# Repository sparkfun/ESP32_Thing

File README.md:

SparkFun ESP32 Thing
========================================

[*SparkFun ESP32 Thing (DEV-13907)*](https://www.sparkfun.com/products/13907)

The [SparkFun ESP32 Thing](https://www.sparkfun.com/products/13907) is a comprehensive development platform for Espressif’s ESP32, their super-charged version of the popular ESP8266. Like the 8266, the ESP32 is a WiFi-compatible microcontroller but adds nearly 30 I/O pins. The ESP32’s power and versatility will make it the foundation of IoT and connected projects for many years to come.

Why the name? We lovingly call it the “Thing” because it's the perfect foundation for your Internet of Things project. The Thing does everything from turning on an LED to posting data with your chosen platform, and can be programmed just like any microcontroller. You can even program the Thing through the Arduino IDE by installing the [ESP32 Arduino Core](https://learn.sparkfun.com/tutorials/esp32-thing-hookup-guide#installing-the-esp32-arduino-core).

The SparkFun ESP32 Thing equips the ESP32 with everything necessary to program, run and develop on the wonderchip. In addition to the WiFi SoC, the Thing includes an FTDI FT231x, which converts USB to serial, and allows your computer to program and communicate with the microcontroller. It also features a LiPo charger, so your ESP32 project can be battery-powered and truly wireless. Additionally, the board includes a handful of LEDs and buttons to aid in your development.

Repository Contents
-------------------

* **/Hardware** - Eagle design files (.brd, .sch)
* **/Production** - Production panel files (.brd)

Documentation
--------------
* **[Hookup Guide](https://learn.sparkfun.com/tutorials/esp32-thing-hookup-guide)** - Basic hookup guide for the ESP32 Thing.
* **[SparkFun Fritzing repo](https://github.com/sparkfun/Fritzing_Parts)** - Fritzing diagrams for SparkFun products.
* **[SparkFun 3D Model repo](https://github.com/sparkfun/3D_Models)** - 3D models of SparkFun products. 
* **[SparkFun Graphical Datasheets](https://github.com/sparkfun/Graphical_Datasheets)** -Graphical Datasheets for various SparkFun products.

Product Versions
----------------
* [DEV-13907](https://www.sparkfun.com/products/13907) - Initial release of the ESP32 Thing.

Version History
---------------
* [V_1.0](https://github.com/sparkfun/ESP32_Thing/releases/tag/V_1.0) - Initial release of the ESP32 Thing

License Information
-------------------

This product is _**open source**_! 

Please review the LICENSE.md file for license information. 

If you have any questions or concerns on licensing, please contact technical support on our [SparkFun forums](https://forum.sparkfun.com/viewforum.php?f=152).

Distributed as-is; no warranty is given.

- Your friends at SparkFun.

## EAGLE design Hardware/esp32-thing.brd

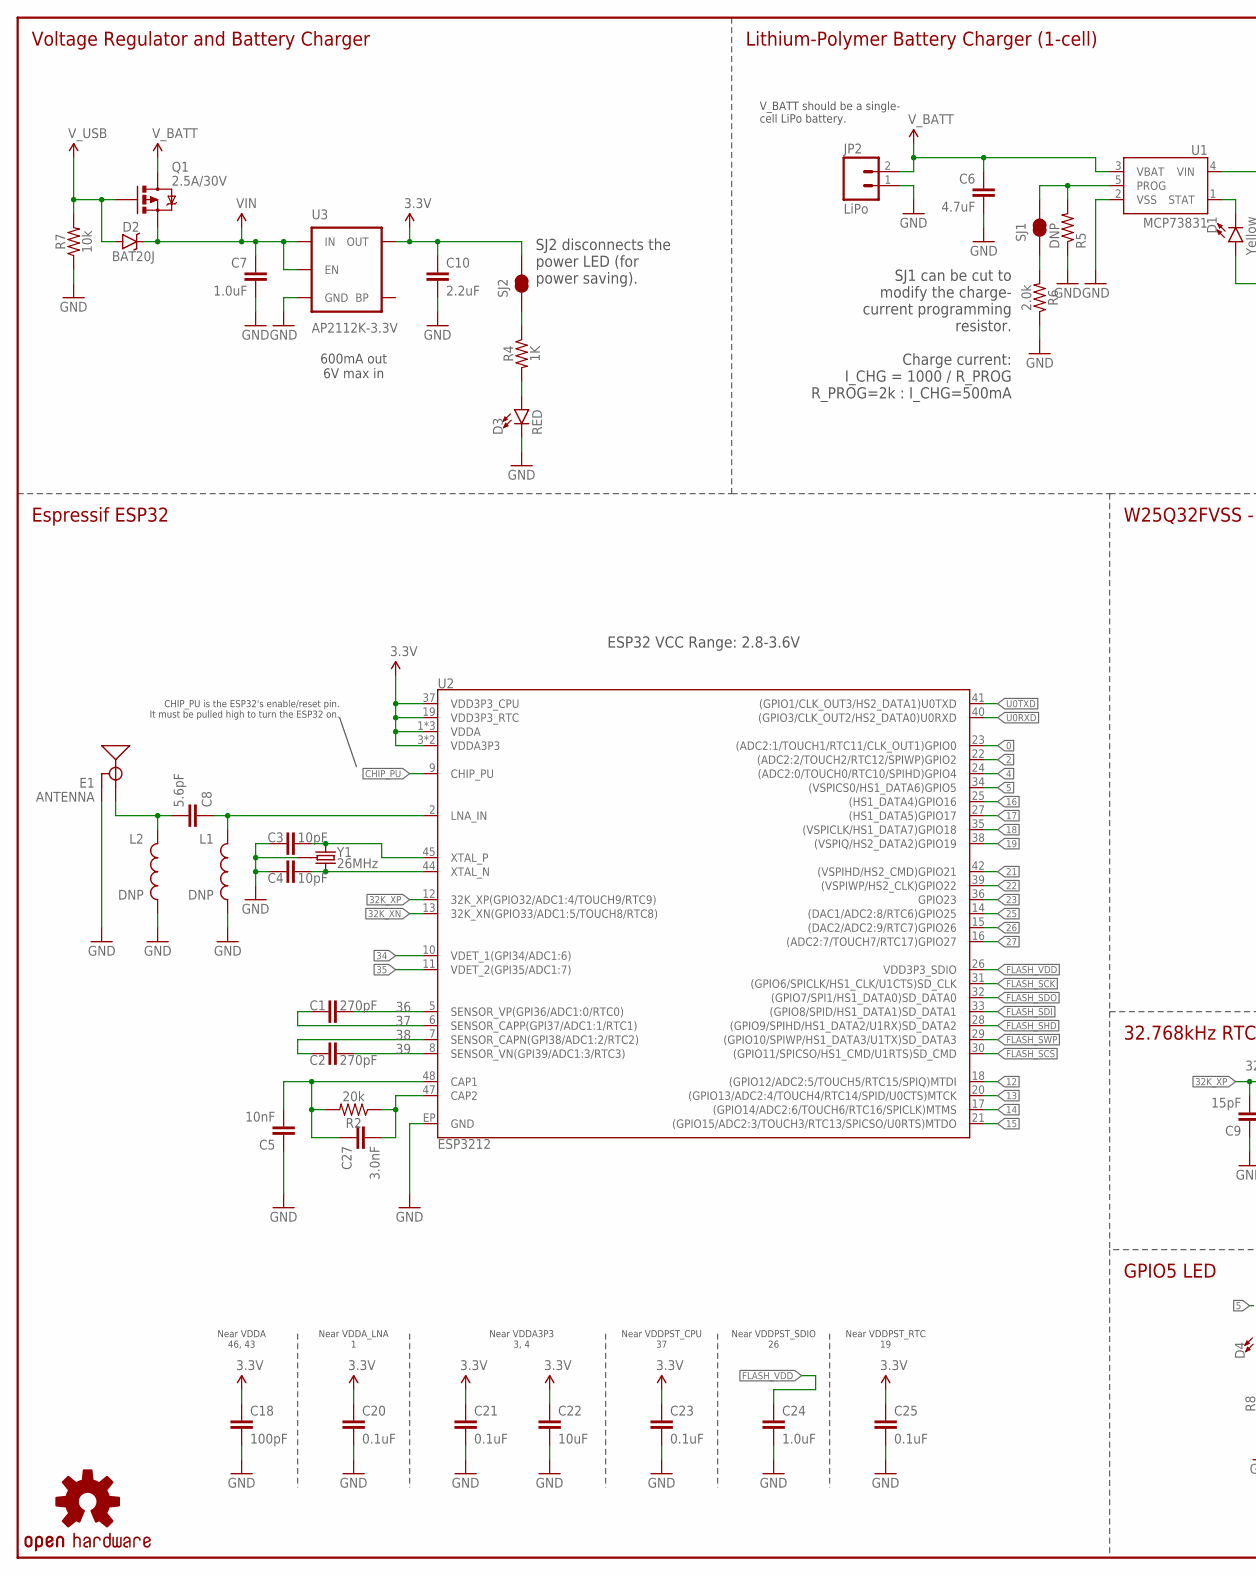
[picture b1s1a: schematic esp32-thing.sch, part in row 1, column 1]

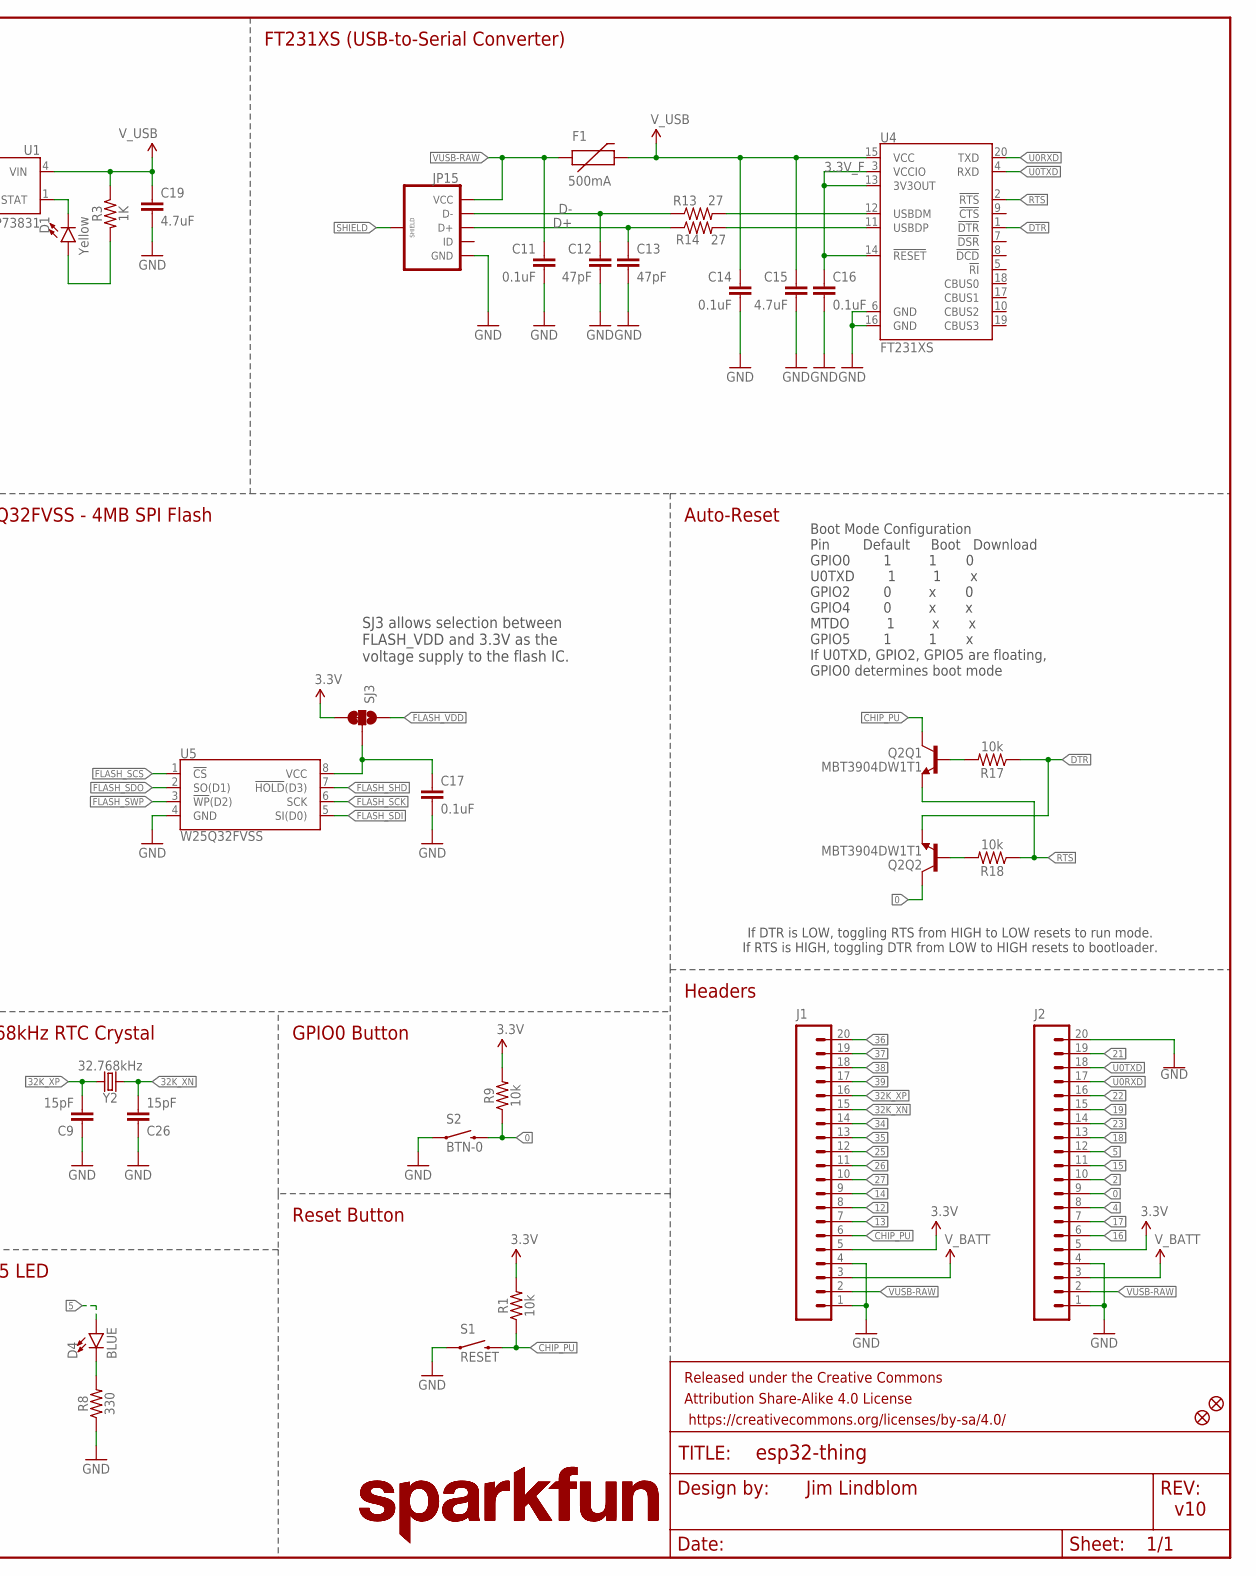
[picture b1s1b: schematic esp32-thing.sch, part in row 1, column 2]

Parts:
C1, C2: 270pF; 0603
C3, C4: 10pF; 0603
C5: 10nF; 0603
C6, C19: 4.7uF; 0603
C7: 1.0uF; 0805
C8: 5.6pF; 0603
C9, C26: 15pF; 0603
C10: 2.2uF; 0603
C11, C14, C16, C17, C20, C21, C23, C25: 0.1uF; 0603
C12, C13: 47pF; 0603
C15: 4.7uF; 0603-CAP
C18: 100pF; 0603
C22: 10uF; 0603
C24: 1.0uF; 0603
C27: 3.0nF; 0603
D1: Yellow; LED-0603
D2: BAT20J; SOD-323
D3: RED; LED-0603
D4: BLUE; LED-0603
E1: ANTENNA; TRACE_ANTENNA_2.4GHZ_25.7MM_TUNED
F1: 500mA; PTC-1206
FD1, FD2: FIDUCIALUFIDUCIAL; MICRO-FIDUCIAL
FRAME1: FRAME-LEDGER; CREATIVE_COMMONS
J1, J2: M20NOSILK; 1X20_NOSILK
JP2: LiPo; JST-2-PTH
JP15: USB_MICROB_PLUGCONN-11752; USB-B-MICRO-SMD_V03
L1, L2: DNP; 0603
LOGO1, LOGO3: SFE_LOGO_NAME.2_INCH; SFE_LOGO_NAME_.2
LOGO2: OSHW-LOGOMINI; OSHW-LOGO-MINI
Q1: 2.5A/30V; SOT23-3
Q2: MBT3904DW1T1; SC70-6
R1, R7, R9, R17, R18: 10k; 0603
R2: 20k; 0603
R3, R4: 1K; 0603
R5: DNP; 1/6W-RES
R6: 2.0k; 0603
R8: 330; 0603
R13, R14: 27; 0603
S1: RESET; TACTILE_SWITCH_SMD_4.6X2.8MM
S2: BTN-0; TACTILE_SWITCH_SMD_4.6X2.8MM
SJ1, SJ2: JUMPER-PAD-2-NC_BY_TRACE; PAD-JUMPER-2-NC_BY_TRACE_YES_SILK
SJ3: JUMPER-PAD-3-2OF3_NC_BY_TRACE_SMALL; PAD-JUMPER-3-2OF3_NC_BY_TRACE_YES_SILK_FULL_BOX
U1: MCP73831; SOT23-5
U2: ESP3212; QFN48-0.4MM
U3: AP2112K-3.3V; SOT23-5
U4: FT231XS; SSOP20_L
U5: W25Q32FVSS; SOIC-8
Y1: 26MHz; CRYSTAL-SMD-3.2X2.5
Y2: 32.768kHz; CRYSTAL-SMD-3.2X1.5MM

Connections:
0: J2.9, Q2.6 (C), R9.1, S2.3 (2), S2.4 (2), U2.23 ((ADC2:1/TOUCH1/RTC11/CLK_OUT1)GPIO0)
2: J2.10, U2.22 ((ADC2:2/TOUCH2/RTC12/SPIWP)GPIO2)
3.3V: C10.1, C18.1, C20.1, C21.1, C22.1, C23.1, C25.1, J1.5, J2.5, R1.2, R9.2, SJ2.2, SJ3.3, U2.1 (VDDA), U2.3 (VDDA3P3), U2.4 (VDDA3P3), U2.19 (VDD3P3_RTC), U2.37 (VDD3P3_CPU), U2.43 (VDDA), U2.46 (VDDA), U3.5 (OUT)
3.3V_F: C16.1, U4.3 (VCCIO), U4.13 (3V3OUT), U4.14 (!RESET)
4: J2.8, U2.24 ((ADC2:0/TOUCH0/RTC10/SPIHD)GPIO4)
5: D4.A, J2.12, U2.34 ((VSPICS0/HS1_DATA6)GPIO5)
12: J1.8, U2.18 ((GPIO12/ADC2:5/TOUCH5/RTC15/SPIQ)MTDI)
13: J1.7, U2.20 ((GPIO13/ADC2:4/TOUCH4/RTC14/SPID/U0CTS)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)
14: J1.9, U2.17 ((GPIO14/ADC2:6/TOUCH6/RTC16/SPICLK)MTMS)
15: J2.11, U2.21 ((GPIO15/ADC2:3/TOUCH3/RTC13/SPICSO/U0RT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)
16: J2.6, U2.25 ((HS1_DATA4)GPIO16)
17: J2.7, U2.27 ((HS1_DATA5)GPIO17)
18: J2.13, U2.35 ((VSPICLK/HS1_DATA7)GPIO18)
19: J2.15, U2.38 ((VSPIQ/HS2_DATA2)GPIO19)
21: J2.19, U2.42 ((VSPIHD/HS2_CMD)GPIO21)
22: J2.16, U2.39 ((VSPIWP/HS2_CLK)GPIO22)
23: J2.14, U2.36 (GPIO23)
25: J1.12, U2.14 ((DAC1/ADC2:8/RTC6)GPIO25)
26: J1.11, U2.15 ((DAC2/ADC2:9/RTC7)GPIO26)
27: J1.10, U2.16 ((ADC2:7/TOUCH7/RTC17)GPIO27)
32K_XN: C26.2, J1.15, U2.13 (32K_XN(GPIO33/ADC1:5/TOUCH8/RTC8)), Y2.P$2 (2)
32K_XP: C9.2, J1.16, U2.12 (32K_XP(GPIO32/ADC1:4/TOUCH9/RTC9)), Y2.P$1 (1)
34: J1.14, U2.10 (VDET_1(GPI34/ADC1:6))
35: J1.13, U2.11 (VDET_2(GPI35/ADC1:7))
36: C1.2, J1.20, U2.5 (SENSOR_VP(GPI36/ADC1:0/RTC0))
37: C1.1, J1.19, U2.6 (SENSOR_CAPP(GPI37/ADC1:1/RTC1))
38: C2.1, J1.18, U2.7 (SENSOR_CAPN(GPI38/ADC1:2/RTC2))
39: C2.2, J1.17, U2.8 (SENSOR_VN(GPI39/ADC1:3/RTC3))
CAP_10N: C5.2, C27.1, R2.2, U2.48 (CAP1)
CHIP_PU: J1.6, Q2.3 (C), R1.1, S1.3 (2), S1.4 (2), U2.9 (CHIP_PU)
D+: C13.1, JP15.D+, R14.1
D-: C12.1, JP15.D-, R13.1
DTR: Q2.1 (E), R17.1, U4.1 (!DTR)
FLASH_SCK: U2.31 ((GPIO6/SPICLK/HS1_CLK/U1CTS)SD_CLK), U5.6 (SCK)
FLASH_SCS: U2.30 ((GPIO11/SPICSO/HS1_CMD/U1RTS)SD_CMD), U5.1 (!CS!)
FLASH_SDI: U2.33 ((GPIO8/SPID/HS1_DATA1)SD_DATA1), U5.5 (SI(D0))
FLASH_SDO: U2.32 ((GPIO7/SPI1/HS1_DATA0)SD_DATA0), U5.2 (SO(D1))
FLASH_SHD: U2.28 ((GPIO9/SPIHD/HS1_DATA2/U1RX)SD_DATA2), U5.7 (!HOLD!(D3))
FLASH_SWP: U2.29 ((GPIO10/SPIWP/HS1_DATA3/U1TX)SD_DATA3), U5.3 (!WP!(D2))
FLASH_VDD: C24.1, SJ3.1, U2.26 (VDD3P3_SDIO)
GND: C3.1, C4.1, C5.1, C6.2, C7.2, C9.1, C10.2, C11.2, C12.2, C13.2, C14.2, C15.2, C16.2, C17.2, C18.2, C19.2, C20.2, C21.2, C22.2, C23.2, C24.2, C25.2, C26.1, D3.C, E1.GND, E1.GND2 (GND), J1.1, J1.4, J2.1, J2.4, J2.20, JP2.1, JP15.GND, L1.2, L2.2, R5.1, R6.1, R7.1, R8.1, S1.1, S1.2 (1), S2.1, S2.2 (1), U1.2 (VSS), U2.EP (GND), U3.2 (GND), U4.6 (GND), U4.16 (GND), U5.4 (GND), Y1.2 (GND), Y1.4 (GND)
LNA_IN: C8.1, L1.1, U2.2 (LNA_IN)
unnamed: D4.C, R8.2
unnamed: D3.A, R4.2
unnamed: R4.1, SJ2.1
unnamed: C27.2, R2.1, U2.47 (CAP2)
unnamed: R13.2, U4.12 (USBDM)
unnamed: R14.2, U4.11 (USBDP)
unnamed: D1.C, U1.1 (STAT)
unnamed: Q2.5 (B), R17.2
unnamed: C17.1, SJ3.2, U5.8 (VCC)
unnamed: Q2.2 (B), R18.2
unnamed: C3.2, U2.45 (XTAL_P), Y1.1
unnamed: R5.2, SJ1.2, U1.5 (PROG)
unnamed: C4.2, U2.44 (XTAL_N), Y1.3 (2)
unnamed: R6.2, SJ1.1
unnamed: D1.A, R3.2
RTS: Q2.4 (E), R18.1, U4.2 (!RTS)
SHIELD: JP15.SHIELD1 (SHIELD), JP15.SHIELD2 (SHIELD), JP15.SHIELD3 (SHIELD)
TRACE_ANT: C8.2, E1.ANT (SIGNAL), L2.1
U0RXD: J2.17, U2.40 ((GPIO3/CLK_OUT2/HS2_DATA0)U0RXD), U4.20 (TXD)
U0TXD: J2.18, U2.41 ((GPIO1/CLK_OUT3/HS2_DATA1)U0TXD), U4.4 (RXD)
VIN: C7.1, D2.C, Q1.2 (S), U3.1 (IN), U3.3 (EN)
VUSB-RAW: C11.1, F1.1, J1.2, J2.2, JP15.VBUS (VCC)
V_BATT: C6.1, J1.3, J2.3, JP2.2, Q1.3 (D), U1.3 (VBAT)
V_USB: C14.1, C15.1, C19.1, D2.A, F1.2, Q1.1 (G), R3.1, R7.2, U1.4 (VIN), U4.15 (VCC)

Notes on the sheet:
Boot Mode Configuration Pin Default Boot Download GPIO0 1 1 0 U0TXD 1 1 x GPIO2 0 x 0 GPIO4 0 x x MTDO 1 x x GPIO5 1 1 x If U0TXD, GPIO2, GPIO5 are floating, GPIO0 determines boot mode
FT231XS (USB-to-Serial Converter)
V_BATT should be a single- cell LiPo battery.
Charge current: I_CHG = 1000 / R_PROG R_PROG=2k : I_CHG=500mA
Voltage Regulator and Battery Charger
SJ1 can be cut to modify the charge- current programming resistor.
Lithium-Polymer Battery Charger (1-cell)
600mA out 6V max in
Auto-Reset
Near VDDA 46, 43
Near VDDA_LNA 1
Near VDDA3P3 3, 4
Near VDDPST_CPU 37
Near VDDPST_SDIO 26
Near VDDPST_RTC 19
Espressif ESP32
W25Q32FVSS - 4MB SPI Flash
32.768kHz RTC Crystal
GPIO0 Button
Reset Button
GPIO5 LED
Headers
v10
Jim Lindblom
ESP32 VCC Range: 2.8-3.6V
SJ3 allows selection between FLASH_VDD and 3.3V as the voltage supply to the flash IC.
SJ2 disconnects the power LED (for power saving).
If DTR is LOW, toggling RTS from HIGH to LOW resets to run mode. If RTS is HIGH, toggling DTR from LOW to HIGH resets to bootloader.
CHIP_PU is the ESP32's enable/reset pin. It must be pulled high to turn the ESP32 on.

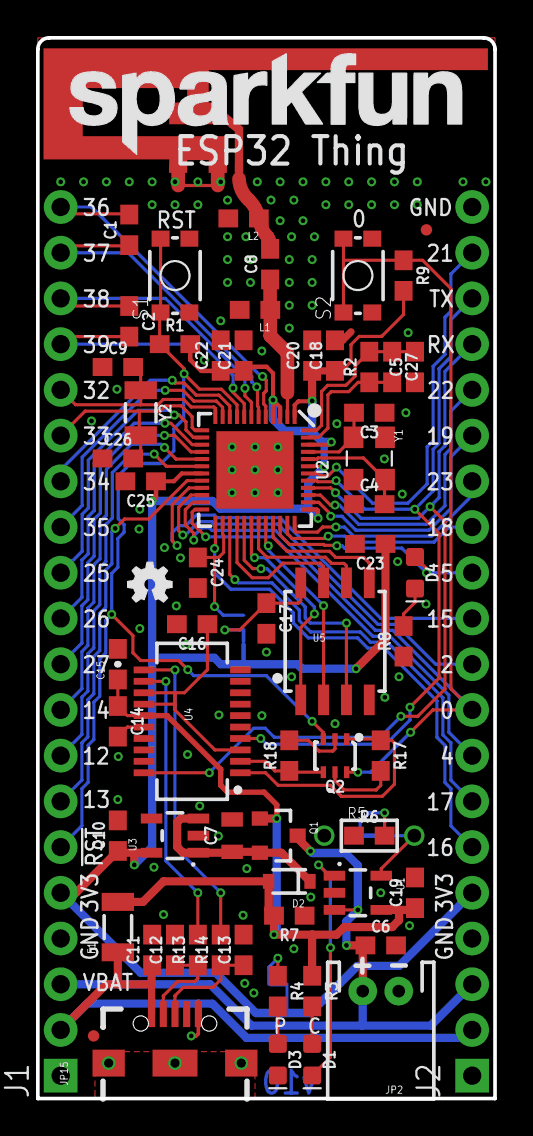
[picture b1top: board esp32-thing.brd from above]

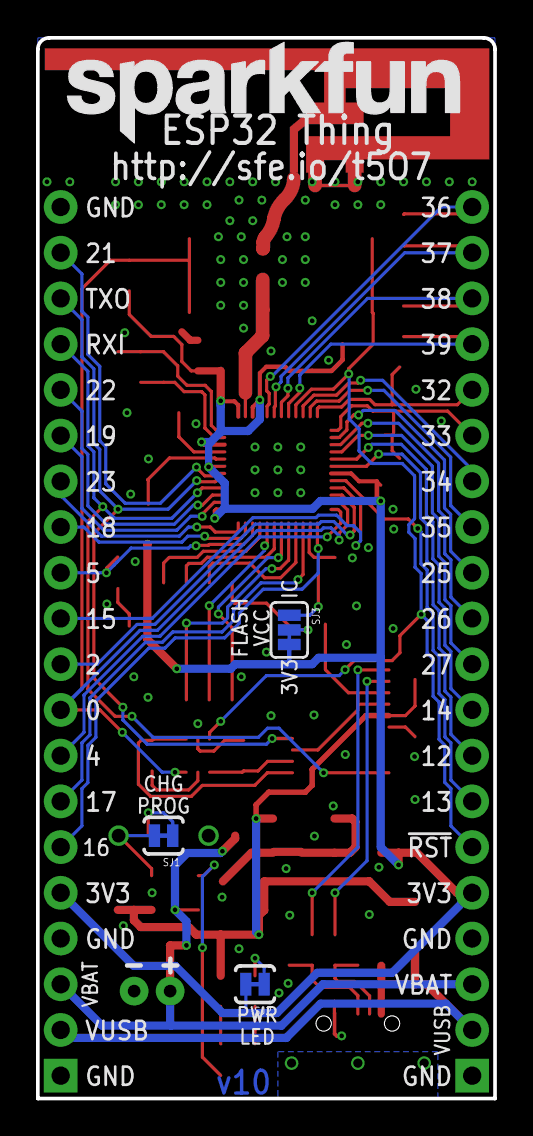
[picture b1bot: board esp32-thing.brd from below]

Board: 2 copper layers, 25.4 x 58.9 mm, 72 parts (4 on the bottom side), 66 nets.

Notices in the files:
parts and their libraries:
SparkFun-Electromechanical: Licensing: Creative Commons ShareAlike 4.0 International - https://creativecommons.org/licenses/by-sa/4.0
SparkFun-Aesthetics: Released under the Creative Commons Attribution Share-Alike 4.0 License
SparkFun-Aesthetics: https://creativecommons.org/licenses/by-sa/4.0
